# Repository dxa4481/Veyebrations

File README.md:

# Veyebrations
We are creating a system that translates measured distances of physical objects into vibrations to assist the blind.

##Finished Prototypes

This image shows all components insde the enclosure

This shows the final PCB used

This is showing all the components mounted onto the PCB

This shows the solder paste being injected uner a microscope

## Breadboard mockups

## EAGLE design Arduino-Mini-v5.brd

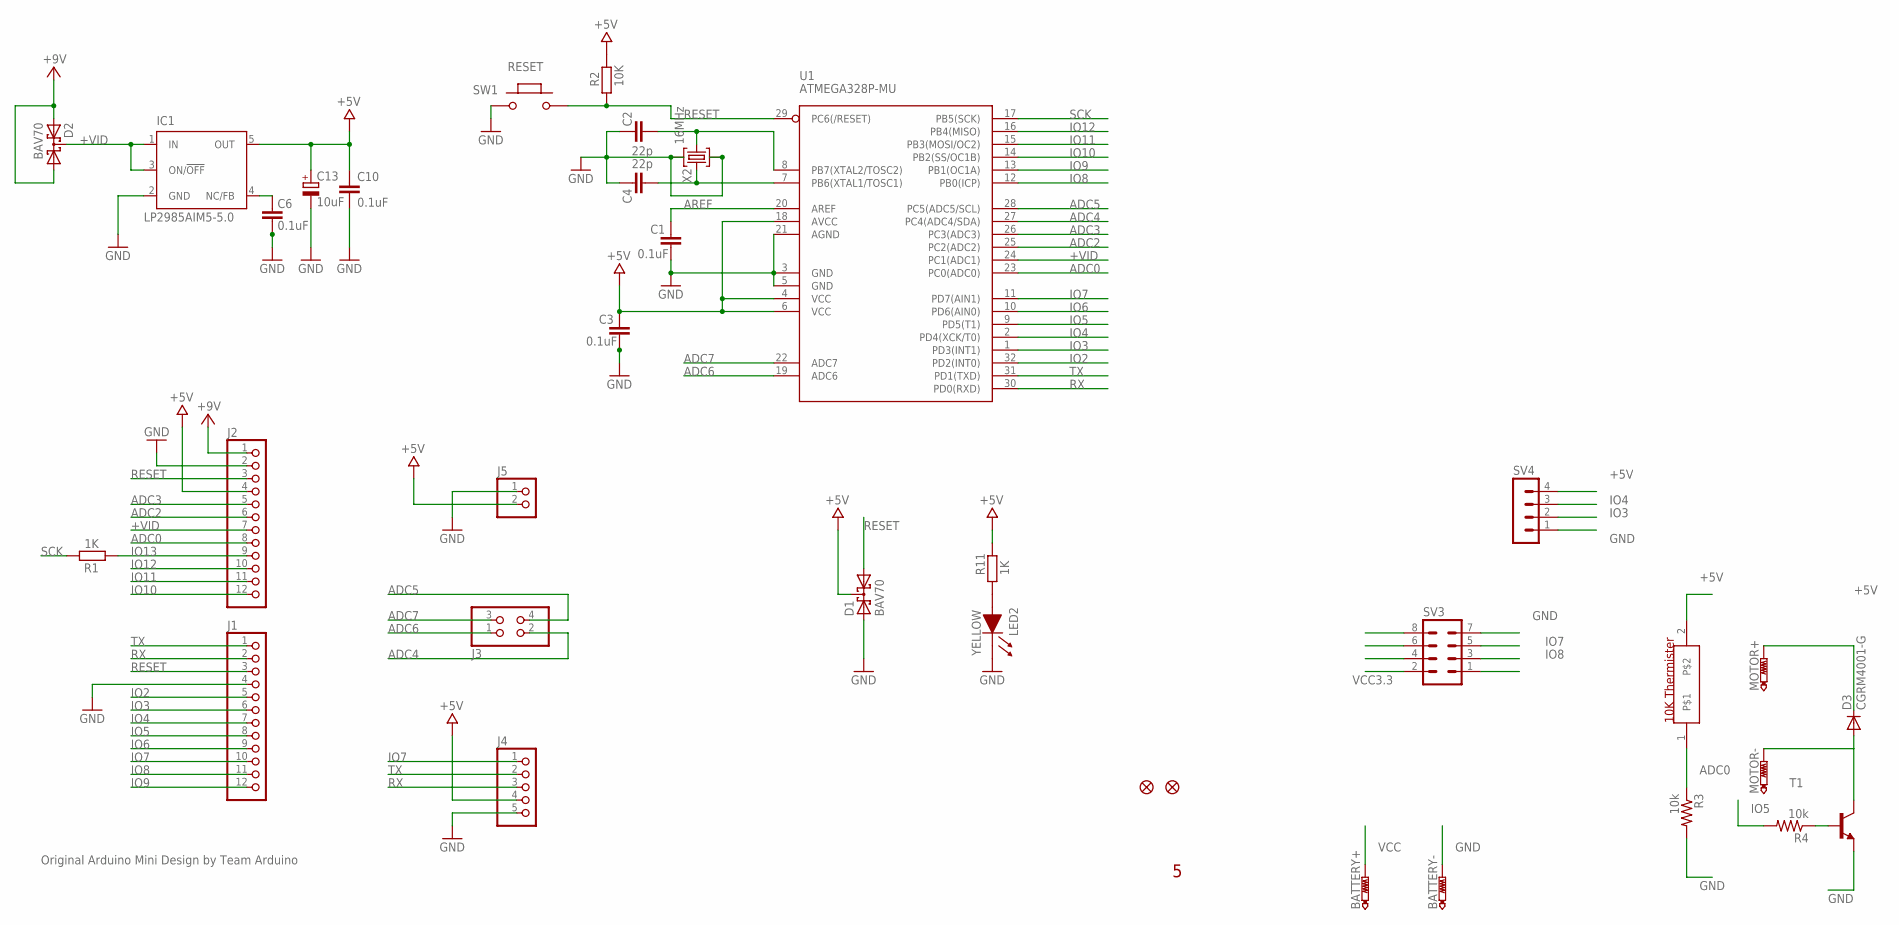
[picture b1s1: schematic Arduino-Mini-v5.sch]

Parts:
BATTERY+: PTR1TP20SQ; TP20SQ
BATTERY-: PTR1TP20SQ; TP20SQ
C1, C3, C6, C10: 0.1uF; C0603-ROUND
C2, C4: 22p; C0603-ROUND
C13: 10uF; SMC_B
D1, D2: BAV70; SOT23
D3: CGRM4001-G; SOD-123_MINI-SMA
IC1: LP2985AIM5-5.0; SOT23-DBV
J1, J2: PINHD-1X12; 1X12
J3: PINHD-2X2; 2X02
J4: PINHD-1X5; 1X5
J5: PINHD-1X2; 1X2
LED2: YELLOW; SMD_LED0805
MOTOR+: PTR1TP20SQ; TP20SQ
MOTOR-: PTR1TP20SQ; TP20SQ
R1, R11: 1K; R0603-ROUND
R2: 10K; R0603-ROUND
R3, R4: 10k; R0603
SV3: MA04-2
SV4: MA04-1
SW1: RESET; SMD_157SW
T1: MMBT3904LT1-NPN-SOT23-BEC; SOT23-BEC
U1: ATMEGA328P-MU; MLF32-M1-A
U$2, U$4: FIDUCIAL1X2; FIDUCIAL-1X2
U$12: NTHS0603N02N1002JE; 0603-RES
X2: 16MHz; CRYSTAL-3.2-2.5

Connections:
+5V: C3.2, C10.1, C13.+, D1.3 (C), D3.C, IC1.5 (OUT), J2.4, J4.4, J5.2, MOTOR+.TP, R2.2, R11.2, SV4.4, U1.4 (VCC), U1.6 (VCC), U1.18 (AVCC), U$12.2
+VID: D2.3 (C), IC1.1 (IN), IC1.3 (ON/!OFF), J2.7, U1.24 (PC1(ADC1))
ADC0: J2.8, R3.1, U1.23 (PC0(ADC0)), U$12.1
ADC2: J2.6, U1.25 (PC2(ADC2))
ADC3: J2.5, U1.26 (PC3(ADC3))
ADC4: J3.2, U1.27 (PC4(ADC4/SDA))
ADC5: J3.4, U1.28 (PC5(ADC5/SCL))
ADC6: J3.1, U1.19 (ADC6)
ADC7: J3.3, U1.22 (ADC7)
AREF: C1.2, U1.20 (AREF)
GND: BATTERY-.TP, C1.1, C2.2, C3.1, C4.2, C6.1, C10.2, C13.-, D1.1 (A1), IC1.2 (GND), J1.4, J2.2, J4.5, J5.1, LED2.1 (CA), R3.2, SV3.7, SV4.1, SW1.1, T1.E, U1.3 (GND), U1.5 (GND), U1.21 (AGND), X2.2 (GND), X2.4 (GND)
IO2: J1.5, U1.32 (PD2(INT0))
IO3: J1.6, SV4.2, U1.1 (PD3(INT1))
IO4: J1.7, SV4.3, U1.2 (PD4(XCK/T0))
IO5: J1.8, R4.2, U1.9 (PD5(T1))
IO6: J1.9, U1.10 (PD6(AIN0))
IO7: J1.10, J4.1, SV3.5, U1.11 (PD7(AIN1))
IO8: J1.11, SV3.3, U1.12 (PB0(ICP))
IO9: J1.12, U1.13 (PB1(OC1A))
IO10: J2.12, U1.14 (PB2(SS/OC1B))
IO11: J2.11, U1.15 (PB3(MOSI/OC2))
IO12: J2.10, U1.16 (PB4(MISO))
IO13: J2.9, R1.1
unnamed: C4.1, U1.7 (PB6(XTAL1/TOSC1)), X2.1 (C1)
unnamed: C2.1, U1.8 (PB7(XTAL2/TOSC2)), X2.3 (C2)
unnamed: C6.2, IC1.4 (NC/FB)
unnamed: LED2.2 (AN), R11.1
unnamed: D3.A, MOTOR-.TP, T1.C
unnamed: R4.1, T1.B
RESET: D1.2 (A2), J1.3, J2.3, R2.1, SW1.2, U1.29 (PC6(/RESET))
RX: J1.2, J4.3, U1.30 (PD0(RXD))
SCK: R1.2, U1.17 (PB5(SCK))
TX: J1.1, J4.2, U1.31 (PD1(TXD))
VCC: BATTERY+.TP, D2.1 (A1), D2.2 (A2), J2.1
VCC3.3: SV3.2

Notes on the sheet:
Original Arduino Mini Design by Team Arduino

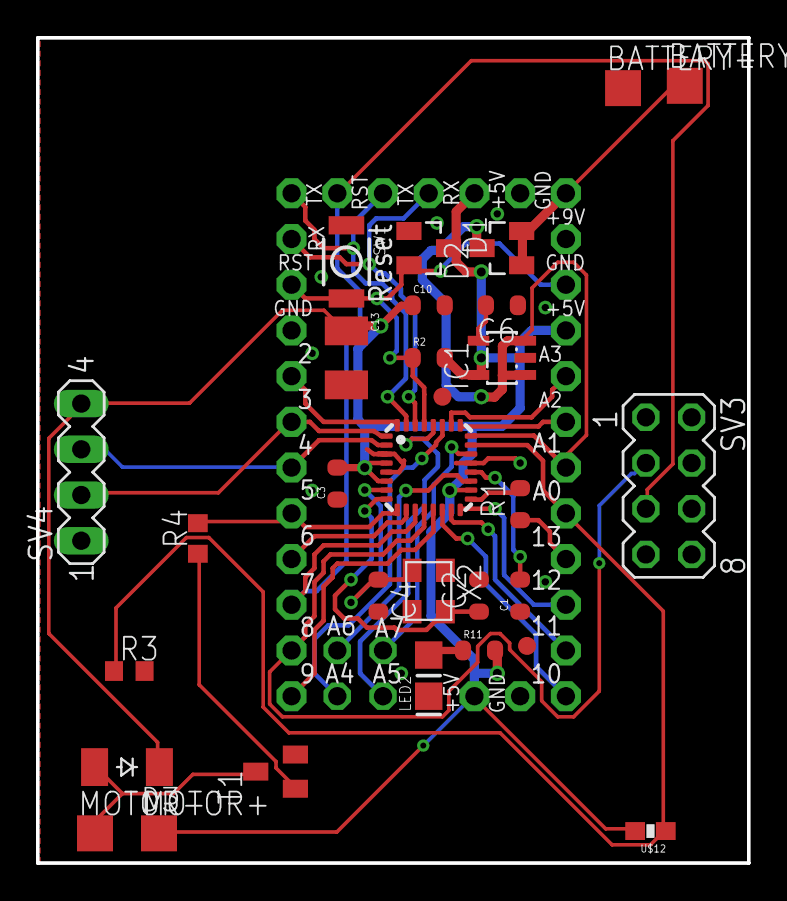
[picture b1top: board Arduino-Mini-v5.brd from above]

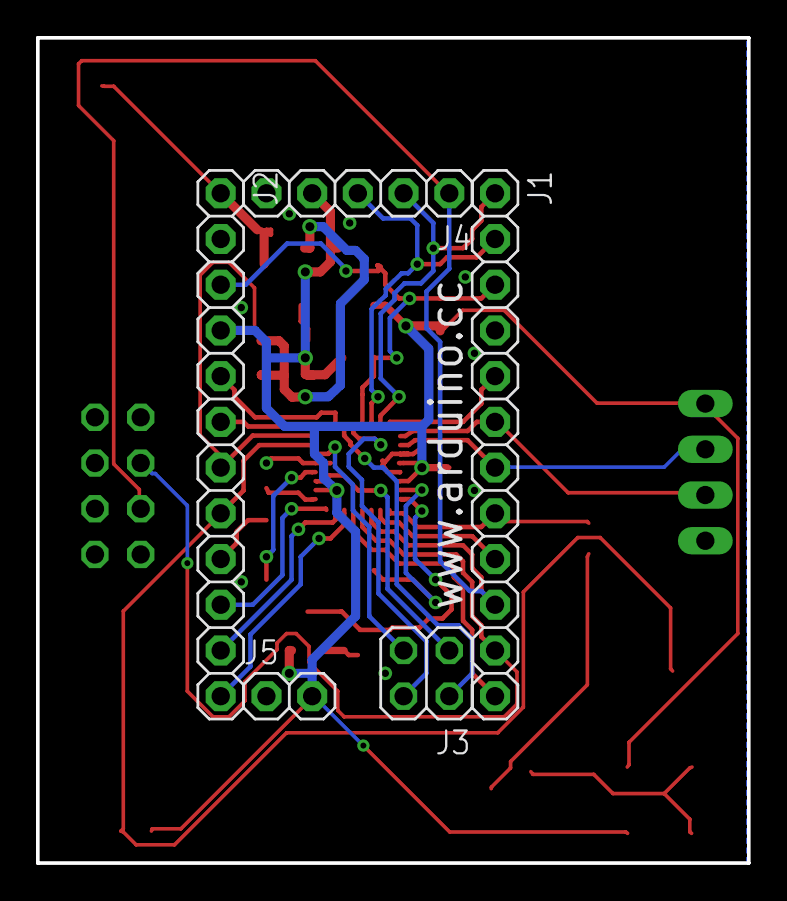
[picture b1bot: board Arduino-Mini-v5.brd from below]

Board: 2 copper layers, 39.5 x 45.8 mm, 35 parts (5 on the bottom side), 34 nets.

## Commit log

2015-08-26 added temperature code
2015-08-29 Create stubs for networking program at a high level.
    I don't know how the devices will be wired, and thus don't know the
    implementation details of, for example, which wire should be set high or
    low, only that a wire needs to represent "Send permission to Atmega" and
    the semantics of the wire representing said concept.
2015-09-02 Add library CuTest
    We don't have a dependency management system, so adding things to the
    repo seems like the only other alternative.
2015-09-02 Add a contactInfo containing only a time, and a find-min method
    And relevant tests. The find-min method will eventually be used to find
    who this should give the 'chirp key' to, when it wants to give the key
    to someone.
2015-09-02 pulled temp code out into library, and tested succesfully on the board
2015-09-02 adding library folder with readme
2015-09-02 fixing file name of readme
2015-09-02 adding proximity library folders
2015-09-02 moved proximity library into proximity library folder
2015-09-02 Move files to match project style
2015-09-02 Add KeyPermissionClient
    an an incomplete method because I want to use interrupts, but can't figure
    out how to deliver the data the interrupt needs to the interrupt
2015-09-03 Added Motor Code
2015-09-08 CPP-ifying ContactInfo
2015-09-08 Add pingTime member; make keyTime private but provide accessors
2015-09-09 Extracting oerating-on-a-list methods from contactInfo.h
2015-09-09 Add ContactInfo::isStale implementation
2015-09-09 Rename everything
    again
    Why did I put 'info' in anything's name in the first place?
2015-09-11 Add CuTest library, and a suite runner
2015-09-11 KeyPermissionClient constructor pin initialization
    There is a slightly modified "Arduino.h" offscreen that has all of its
    includes removed, since I didn't want to bother doing whatever it took
    to make those nested includes compile without Arduino IDE's magic
2015-09-11 Abandon attempt to use interrupts; poll for key instead
2015-09-12 moving into an src folder
2015-09-12 moving files back
2015-09-12 Fixed import errors / Wrote test
2015-09-12 Added Veyebrations.ino as main sketch for calling into the Libraries
2015-09-12 Updated test / Fixed Library Code
2015-09-12 modified readme
2015-09-12 Add arduino test sketches
2015-09-14 Move C Tests
2015-09-16 power error that I solved by giving the device external power
2015-09-19 Updated the vibration amount calculation to map to 1/distance
2015-09-20 Add concrete networking code
    Basically, actually performing communications, rather than purely abstract
    stuff.
    I cannot get any c++ compiler to run at all, and as such I have no idea whether
    this compiles, and and even less of an idea whether it is correct.
2015-09-22 Improve compilability of library
2015-09-23 Option tests, except it won't run as it has no access to String
2015-09-24 Update LICENSE
2015-09-24 Make temperature's read pin a constructor parameter rather than hardcoded
2015-10-22 placing parts
2015-10-22 placed parts, no routes
2015-10-22 routed 100% :)
2015-10-22 fixing the thermister flaw
2015-12-12 final revisions, smaller board
2015-12-12 removing old files
2015-12-12 removing cached files
2015-12-12 moving into folder, for master merge
